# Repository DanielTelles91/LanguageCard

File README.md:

# LanguageCard
 An Apple II Language Card. Based on a design by [iz8dwf](https://youtu.be/1KPIAoO1dTU)
 All credits to btb.

How I managed to fix the memory corruption problem: https://www.applefritter.com/content/strange-problem-language-card

## Description

This is a simple "language card" for the Apple II and II+, which expands the system from 48K to 64K by means of 16K of RAM, switchable into the address space normally used by the system firmware. That's two banks of 4K in the D0-D8 space, and one bank of 8K in the E0-F8 space. The C0-C8 space is not touched.

It uses static RAM so there is no need for the ribbon cable connecting it to the logic board that the original language cards had.

Like the original language cards, it can also contain a chip that will be used to replace the F8 ROM on your logic board. Additionally, you can enable or disable this replacement ROM with a switch or jumpers. If configured correctly, you can put two different F8 ROM images on a single chip and switch back and forth between them.

## Build Notes

### R3, R4, R5

Use higher resistance for	high-efficiency LEDs, e.g. 3.3K

### U8 and U9

Any narrow 8KBx8	static RAM can be used.	ex: 5C6408, Cy7C185, TC5588

### U7

Optional. 2K or larger	(E)EPROM for overriding the	logic board's F8 ROM. Enable	using SW1 or JP1.

### SW1

Optional Toggle switch. Miniature, Sub-miniature, or Ultra-miniature, right angle, SPDT. (Sub, Ultra-mini use JP1 pads)

An SPST switch which only closes the outer two pin positions can also work if you short JP3. 

To switch between two different F8 ROM images on a single 4K or greater chip, short JP2 and use a	DPDT switch instead - must be a three-position center OFF switch (ON-OFF-ON) in order to disable the card ROM and use the logic board F8 ROM.

### JP1

Enable and select which F8 ROM to use (if not using SW1)

| | |
|-|-|
|6|5|
|4|3|
|2|1|

No Jumpers: Card ROM disabled

#### Using a single ROM image:

JP2 open, Jumper on pins 1,3 (lower right): Card ROM enabled

#### Using two ROM images on a 4K or larger ROM:

JP2 shorted, Jumper on pins 1,3 (lower right) and 2,4 (lower left): Upper ROM image enabled (A11 high)

JP2 shorted, Jumper on pins 3,5 (upper right) and 4,6 (upper left): Lower ROM image enabled (A11 low)

### Solder Jumper JP2
Short, and install DPDT switch	(or use pair of jumpers as above) for	ability to select two different F8	ROM images on a single (4K or larger) ROM. 

### Solder Jumper JP3
Short if using an SPST switch	that only connects outer two pins

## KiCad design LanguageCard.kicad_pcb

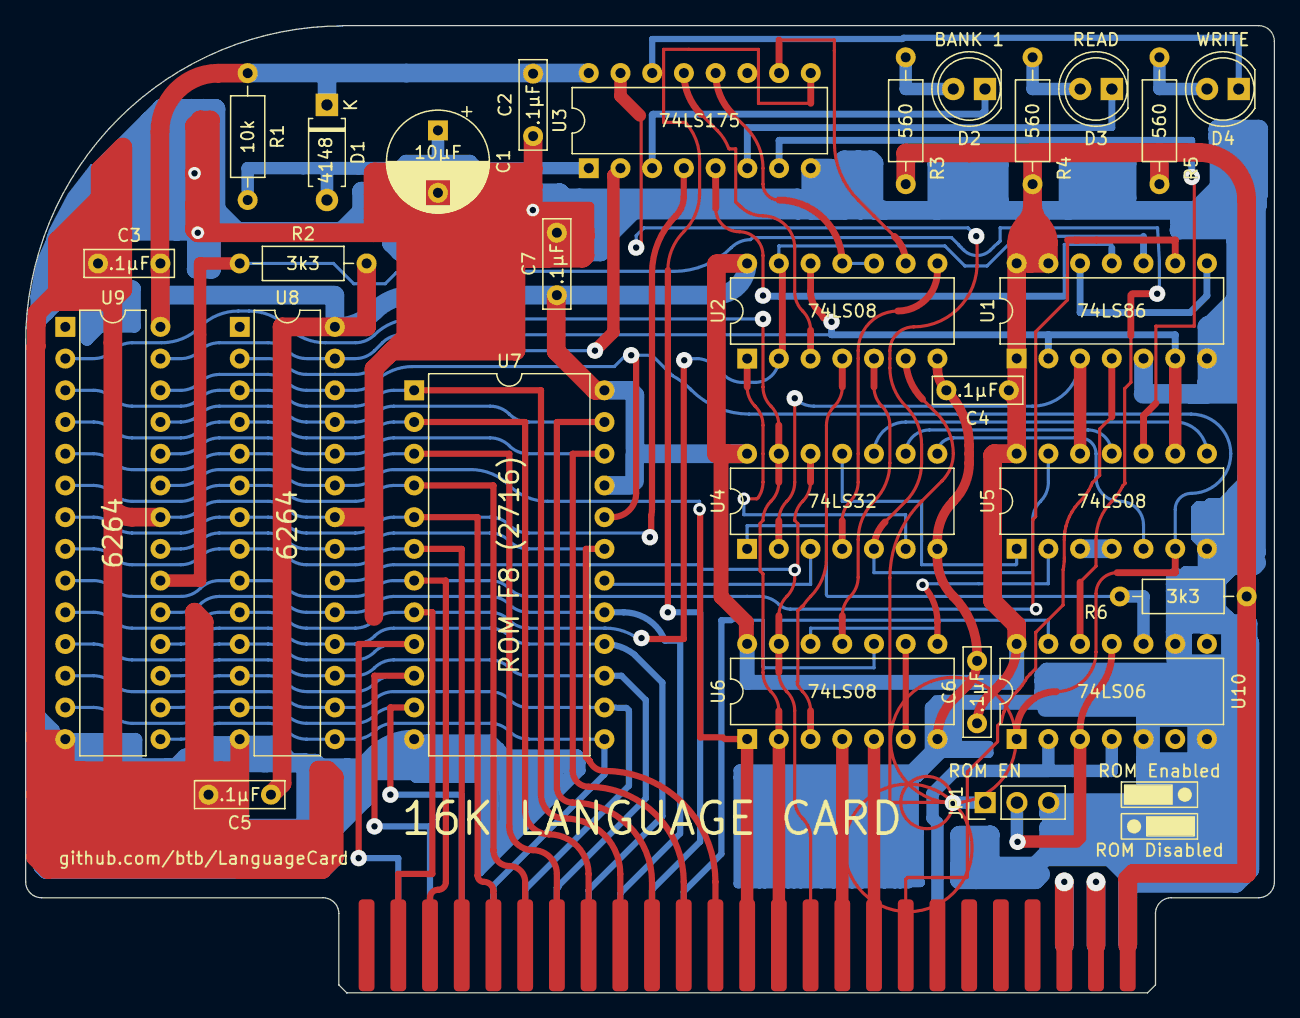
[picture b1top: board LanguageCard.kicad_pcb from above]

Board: 2 copper layers, 100.0 x 77.5 mm, 29 parts (0 on the bottom side), 66 nets.

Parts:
C1: 10μF; CP_Radial_D8.0mm_P5.00mm
C2, C3, C4, C5, C6, C7: .1μF; C_Rect_L7.0mm_W2.0mm_P5.00mm
D1: 4148; D_A-405_P7.62mm_Horizontal
D2: BANK 1; LED_D5.0mm
D3: READ; LED_D5.0mm
D4: WRITE; LED_D5.0mm
J1: Apple II Expansion Bus; Apple II Expansion Edge Connector
JP1: ROM EN; PinHeader_1x03_P2.54mm_Vertical
R1: 10k; R_Axial_DIN0207_L6.3mm_D2.5mm_P10.16mm_Horizontal
R2, R6: 3k3; R_Axial_DIN0207_L6.3mm_D2.5mm_P10.16mm_Horizontal
R3, R4, R5: 560; R_Axial_DIN0207_L6.3mm_D2.5mm_P10.16mm_Horizontal
U1: 74LS86; DIP-14_W7.62mm
U2, U5, U6: 74LS08; DIP-14_W7.62mm
U3: 74LS175; DIP-16_W7.62mm
U4: 74LS32; DIP-14_W7.62mm
U7: ROM F8 (2716); DIP-24_W15.24mm
U8, U9: 6264; DIP-28_W7.62mm
U10: 74LS06; DIP-14_W7.62mm

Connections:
+5V: C2.2, C3.2, C4.1, C5.1, C6.1, C7.1, D1.1 (K), J1.25, R1.1, R2.2, R3.2, R4.2, R5.2, R6.2, U1.1, U1.13, U1.14 (VCC), U2.14 (VCC), U3.16 (VCC), U4.14 (VCC), U5.14 (VCC), U6.14 (VCC), U7.21 (VPP), U7.24 (VCC), U8.28 (VCC), U9.28 (VCC), U10.14 (VCC)
/A0: J1.2, U1.10, U2.2, U2.13, U7.8 (A0), U8.10 (A0), U9.10 (A0)
/A1: J1.3, U1.9, U7.7 (A1), U8.9 (A1), U9.9 (A1)
/A2: J1.4, U7.6 (A2), U8.8 (A2), U9.8 (A2)
/A3: J1.5, U3.4 (D0), U7.5 (A3), U8.7 (A3), U9.7 (A3)
/A4: J1.6, U7.4 (A4), U8.6 (A4), U9.6 (A4)
/A5: J1.7, U7.3 (A5), U8.5 (A5), U9.5 (A5)
/A6: J1.8, U7.2 (A6), U8.4 (A6), U9.4 (A6)
/A7: J1.9, U7.1 (A7), U8.3 (A7), U9.3 (A7)
/A8: J1.10, U7.23 (A8), U8.25 (A8), U9.25 (A8)
/A9: J1.11, U7.22 (A9), U8.24 (A9), U9.24 (A9)
/A10: J1.12, U7.19 (A10), U8.21 (A10), U9.21 (A10)
/A11: J1.13, U6.1, U8.23 (A11), U9.23 (A11)
/A12: J1.14, U4.13, U6.2, U9.2 (A12)
/A13: J1.15, U4.12, U6.13, U8.20 (~CE), U10.13
/A14: J1.16, U6.4
/A15: J1.17, U6.5
/ABNK: U3.2 (Q0), U8.2 (A12)
/BR/W: U1.2, U1.6, U2.12, U5.9, U8.27 (~WE), U9.27 (~WE)
/D0: J1.49, U7.9 (D0), U8.11 (Q0), U9.11 (Q0)
/D1: J1.48, U7.10 (D1), U8.12 (Q1), U9.12 (Q1)
/D2: J1.47, U7.11 (D2), U8.13 (Q2), U9.13 (Q2)
/D3: J1.46, U7.13 (D3), U8.15 (Q3), U9.15 (Q3)
/D4: J1.45, U7.14 (D4), U8.16 (Q4), U9.16 (Q4)
/D5: J1.44, U7.15 (D5), U8.17 (Q5), U9.17 (Q5)
/D6: J1.43, U7.16 (D6), U8.18 (Q6), U9.18 (Q6)
/D7: J1.42, U7.17 (D7), U8.19 (Q7), U9.19 (Q7)
/DFP: U5.3, U5.4
/NEXT: U2.9, U3.10 (Q2)
/PHI0: J1.40, U6.10
/RAMCE: U5.6, U7.20 (~OE), U8.26 (CE2), U9.26 (CE2), U10.1
/RAMEN: U3.7 (Q1), U5.10
/ROM: JP1.2 (C), U10.3, U10.11
/ROMCE: JP1.1 (A), U2.6
/R/W: J1.18, U1.4
/WE: U3.15 (Q3), U4.5, U5.13
/~A13: R2.1, U9.20 (~CE), U10.12
/~ABNK: D2.1 (K), U3.3 (~Q0)
/~DEV: J1.41, U3.9 (Cp)
/~INH: J1.32, U10.2, U10.4
/~RAMEN: D3.1 (K), U3.6 (~Q1)
/~RESET: C1.1, D1.2 (A), R1.2, U3.1 (~Mr)
/~R/W: U1.3, U4.2, U5.12
/~WE: D4.1 (K), U3.14 (~Q3)
GND: C1.2, C2.1, C3.1, C4.2, C5.2, C6.2, C7.2, J1.26, JP1.3 (B), U1.5, U1.7 (GND), U2.7 (GND), U3.8 (GND), U4.7 (GND), U5.7 (GND), U6.7 (GND), U7.12 (GND), U8.14 (GND), U8.22 (~OE), U9.14 (GND), U9.22 (~OE), U10.5, U10.7 (GND), U10.9
unnamed: D2.2 (A), R3.1
unnamed: D3.2 (A), R4.1
unnamed: D4.2 (A), R5.1
unnamed: J1.23, J1.28
unnamed: J1.24, J1.27
unnamed: R6.1, U4.1, U10.10
unnamed: U1.8, U1.12
unnamed: U2.1, U4.6
unnamed: U2.4, U6.3
unnamed: U2.5, U6.11
unnamed: U2.8, U4.4
unnamed: U1.11, U3.5 (D1)
unnamed: U2.10, U2.11, U3.12 (D2)
unnamed: U2.3, U3.13 (D3)
unnamed: U4.8, U5.5
unnamed: U4.9, U5.11
unnamed: U4.10, U5.8
unnamed: U4.11, U5.1
unnamed: U5.2, U6.8, U6.12
unnamed: U6.6, U6.9
unnamed: U4.3, U7.18 (~CE/PGM)

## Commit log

2024-11-28 Mudança de Layout
2024-11-28 Adicionado fotos da placa
